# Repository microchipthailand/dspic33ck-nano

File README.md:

# dsPIC33CK Nano

An open-hardware breadboard board for the Microchip **dsPIC33CK256MC005**
(100 MIPS dsPIC DSC), with an **Arduino-compatible core** and a 30-lab course.

## 📘 Lab manual

| | |
|---|---|
| **Lab manual (English)** | [**Open the lab manual**](https://microchipthailand.github.io/dspic33ck-nano/arduino/dsPIC33CK_Nano_Labs.html): 30 step-by-step labs with wiring diagrams |
| **คู่มือการทดลอง (ภาษาไทย)** | [**เปิดคู่มือภาษาไทย**](https://microchipthailand.github.io/dspic33ck-nano/arduino/dsPIC33CK_Nano_Labs_TH.html) |
| **Pinout page** | [Board pinout and Arduino pin functions](https://microchipthailand.github.io/dspic33ck-nano/arduino/dsPIC33CK_Nano_Pinout.html) |

The labs go from *Basics* (Blink, Serial, ADC, PWM, I2C, SPI) through *Advanced*
(interrupts, timers, DMA, DAC, flash EEPROM, RTOS, watchdog) to *Application*
(data logger, GPS, WS2812B, OLED, Modbus RS485, LIN, CAN, 10BASE-T1S, line-follower
robot, PID temperature control). Every lab has objectives, background theory, a
parts list, a wiring diagram, steps, expected output, a code walk-through,
exercises and troubleshooting.

<sub>If the links above do not open, the pages are also in the repo:
[`arduino/dsPIC33CK_Nano_Labs.html`](arduino/dsPIC33CK_Nano_Labs.html) ·
[`arduino/dsPIC33CK_Nano_Labs_TH.html`](arduino/dsPIC33CK_Nano_Labs_TH.html) ·
[`arduino/dsPIC33CK_Nano_Pinout.html`](arduino/dsPIC33CK_Nano_Pinout.html)
(download, then open in a browser).</sub>

## 📌 Board pinout

Left header **J2**, right header **J3**, both numbered from the USB-C end. The rows
are 0.9" apart, so the board straddles a standard breadboard. Use the Arduino
names (`D5`, `A2`, ...) in sketches.

| Function | Arduino pin | Chip pin | Header |
|---|---|---|---|
| Power out | 3V3 (250 mA) / 5V (USB) | – | J3-1 / J2-1 |
| GND | – | – | J2-2, J3-2 |
| `LED_BUILTIN` (active low) | D34 | RC13 | J2-11 |
| `BUTTON_BUILTIN` (LOW = pressed) | D33 | RC12 | J2-10 |
| `Serial` TX / RX (115200) | D31 / D32 | RC10 / RC11 | J3-4 / J3-3, and UART header J5 |
| I2C `Wire` SDA / SCL | D14 / D13 | RB9 / RB8 | J3-7 / J3-8 |
| SPI SCK / MOSI / MISO / SS | D25 / D26 / D29 / D30 | RC4 / RC5 / RC8 / RC9 | J3-6 / J3-5 / J3-14 / J3-13 |
| `analogWrite()` PWM | D5 / D6 / D7 / D8 | RB0 / RB1 / RB2 / RB3 | J3-21 / J3-20 / J3-17 / J3-16 |
| Analog inputs A0–A4 | A0–A4 (D0–D4) | RA0–RA4 | J2-15 … J2-19 |
| Programming (PICkit / SNAP) | – | MCLR, PGD3 = RB5, PGC3 = RB6 | ICSP header J4 |

All I/O is 3.3 V. Full table with every pin and alternate function: [pinout page](https://microchipthailand.github.io/dspic33ck-nano/arduino/dsPIC33CK_Nano_Pinout.html).

| | |
|---|---|
| MCU | dsPIC33CK256MC005-I/PT, 256 KB flash, 24 KB RAM, internal FRC + PLL (no crystal) |
| Power | USB-C (power only) → MCP1703A 3.3 V LDO |
| Board | 31.4 × 74.5 mm, 2 layers, 2 × 22-pin headers 0.9" apart (fits a breadboard) |
| I/O | user LED RC13, user button RC12, reset button, ICSP header J4 (PICkit/SNAP), UART header J5 |
| Software | Arduino IDE / arduino-cli platform, serial bootloader, 30 example labs |

> **Status:** ERC/DRC clean, Gerbers generated, all labs compile and many were
> checked in the MPLAB simulator. **The board has not been built or tested on
> real hardware yet.**

## Repository layout

```
arduino/                       Arduino-compatible platform + labs + docs
  hardware/dspicnano/dspic33ck/  copy this into <sketchbook>/hardware/
  dsPIC33CK_Nano_Labs.html       step-by-step lab guide with wiring diagrams
  dsPIC33CK_Nano_Pinout.html     pinout page
  tools/                         doc / wiring-diagram generators and checks
pcb/
  kicad/                         KiCad 10 project (schematic, routed PCB, BOM, reports)
  scripts/                       Python generators (design.py = parts and nets)
  fabrication/                   Gerbers + drill (zip ready for the fab), BOM, pick-and-place, PDFs
docs/images/                   renders and pinout image used in this README
LICENSE  NOTICE.md  LICENSES/  licensing and third-party notices
```

## Quick start (Arduino)

1. Install **MPLAB XC-DSC v4.00+** (the free edition is enough) and **MPLAB X**
   (it provides IPE for PICkit uploads) from microchip.com.
2. In the Arduino IDE, open *File → Preferences → Additional boards manager URLs*
   and add:
   ```
   https://raw.githubusercontent.com/microchipthailand/dspic33ck-nano/main/package_dspicnano_index.json
   ```
3. Open *Tools → Board → Boards Manager*, search **dsPIC33CK Nano**, and click
   **Install**. The dsPIC33CK device packs are installed with it.
   (If you are developing the core, copy `arduino/hardware/` into your sketchbook
   instead. Do not use both methods at once.)
4. Pick *Tools → Board → dsPIC33CK Nano (dsPIC33CK256MC005)*, then open
   *File → Examples → dsPIC33CK_Nano → Lab01_Blink* and upload it over a PICkit on J4.

More detail: [`arduino/README.md`](arduino/README.md) and the [lab manual](https://microchipthailand.github.io/dspic33ck-nano/arduino/dsPIC33CK_Nano_Labs.html).

## Ordering the PCB

Upload `pcb/fabrication/dspic33ck_nano_gerbers.zip` to any PCB fab. Use these
settings: 2 layers, 1.6 mm, red mask, HASL. The full spec is in
[`pcb/fabrication/README.txt`](pcb/fabrication/README.txt).

> The top silkscreen has a Microchip logo. Remove it before selling boards; see
> [`NOTICE.md`](NOTICE.md).

## License

- This repository (Arduino core, variant, bootloader, labs, docs, PCB design):
  **MIT**, see [`LICENSE`](LICENSE).
- Microchip linker scripts: Apache-2.0 ([`LICENSES/Apache-2.0.txt`](LICENSES/Apache-2.0.txt)).

## Trademarks

This is an independent, Arduino-compatible project. It is not affiliated with or
endorsed by Arduino SA. "Arduino" is a trademark of Arduino SA. Microchip,
dsPIC, MPLAB, PICkit and Curiosity are trademarks of Microchip Technology Inc.

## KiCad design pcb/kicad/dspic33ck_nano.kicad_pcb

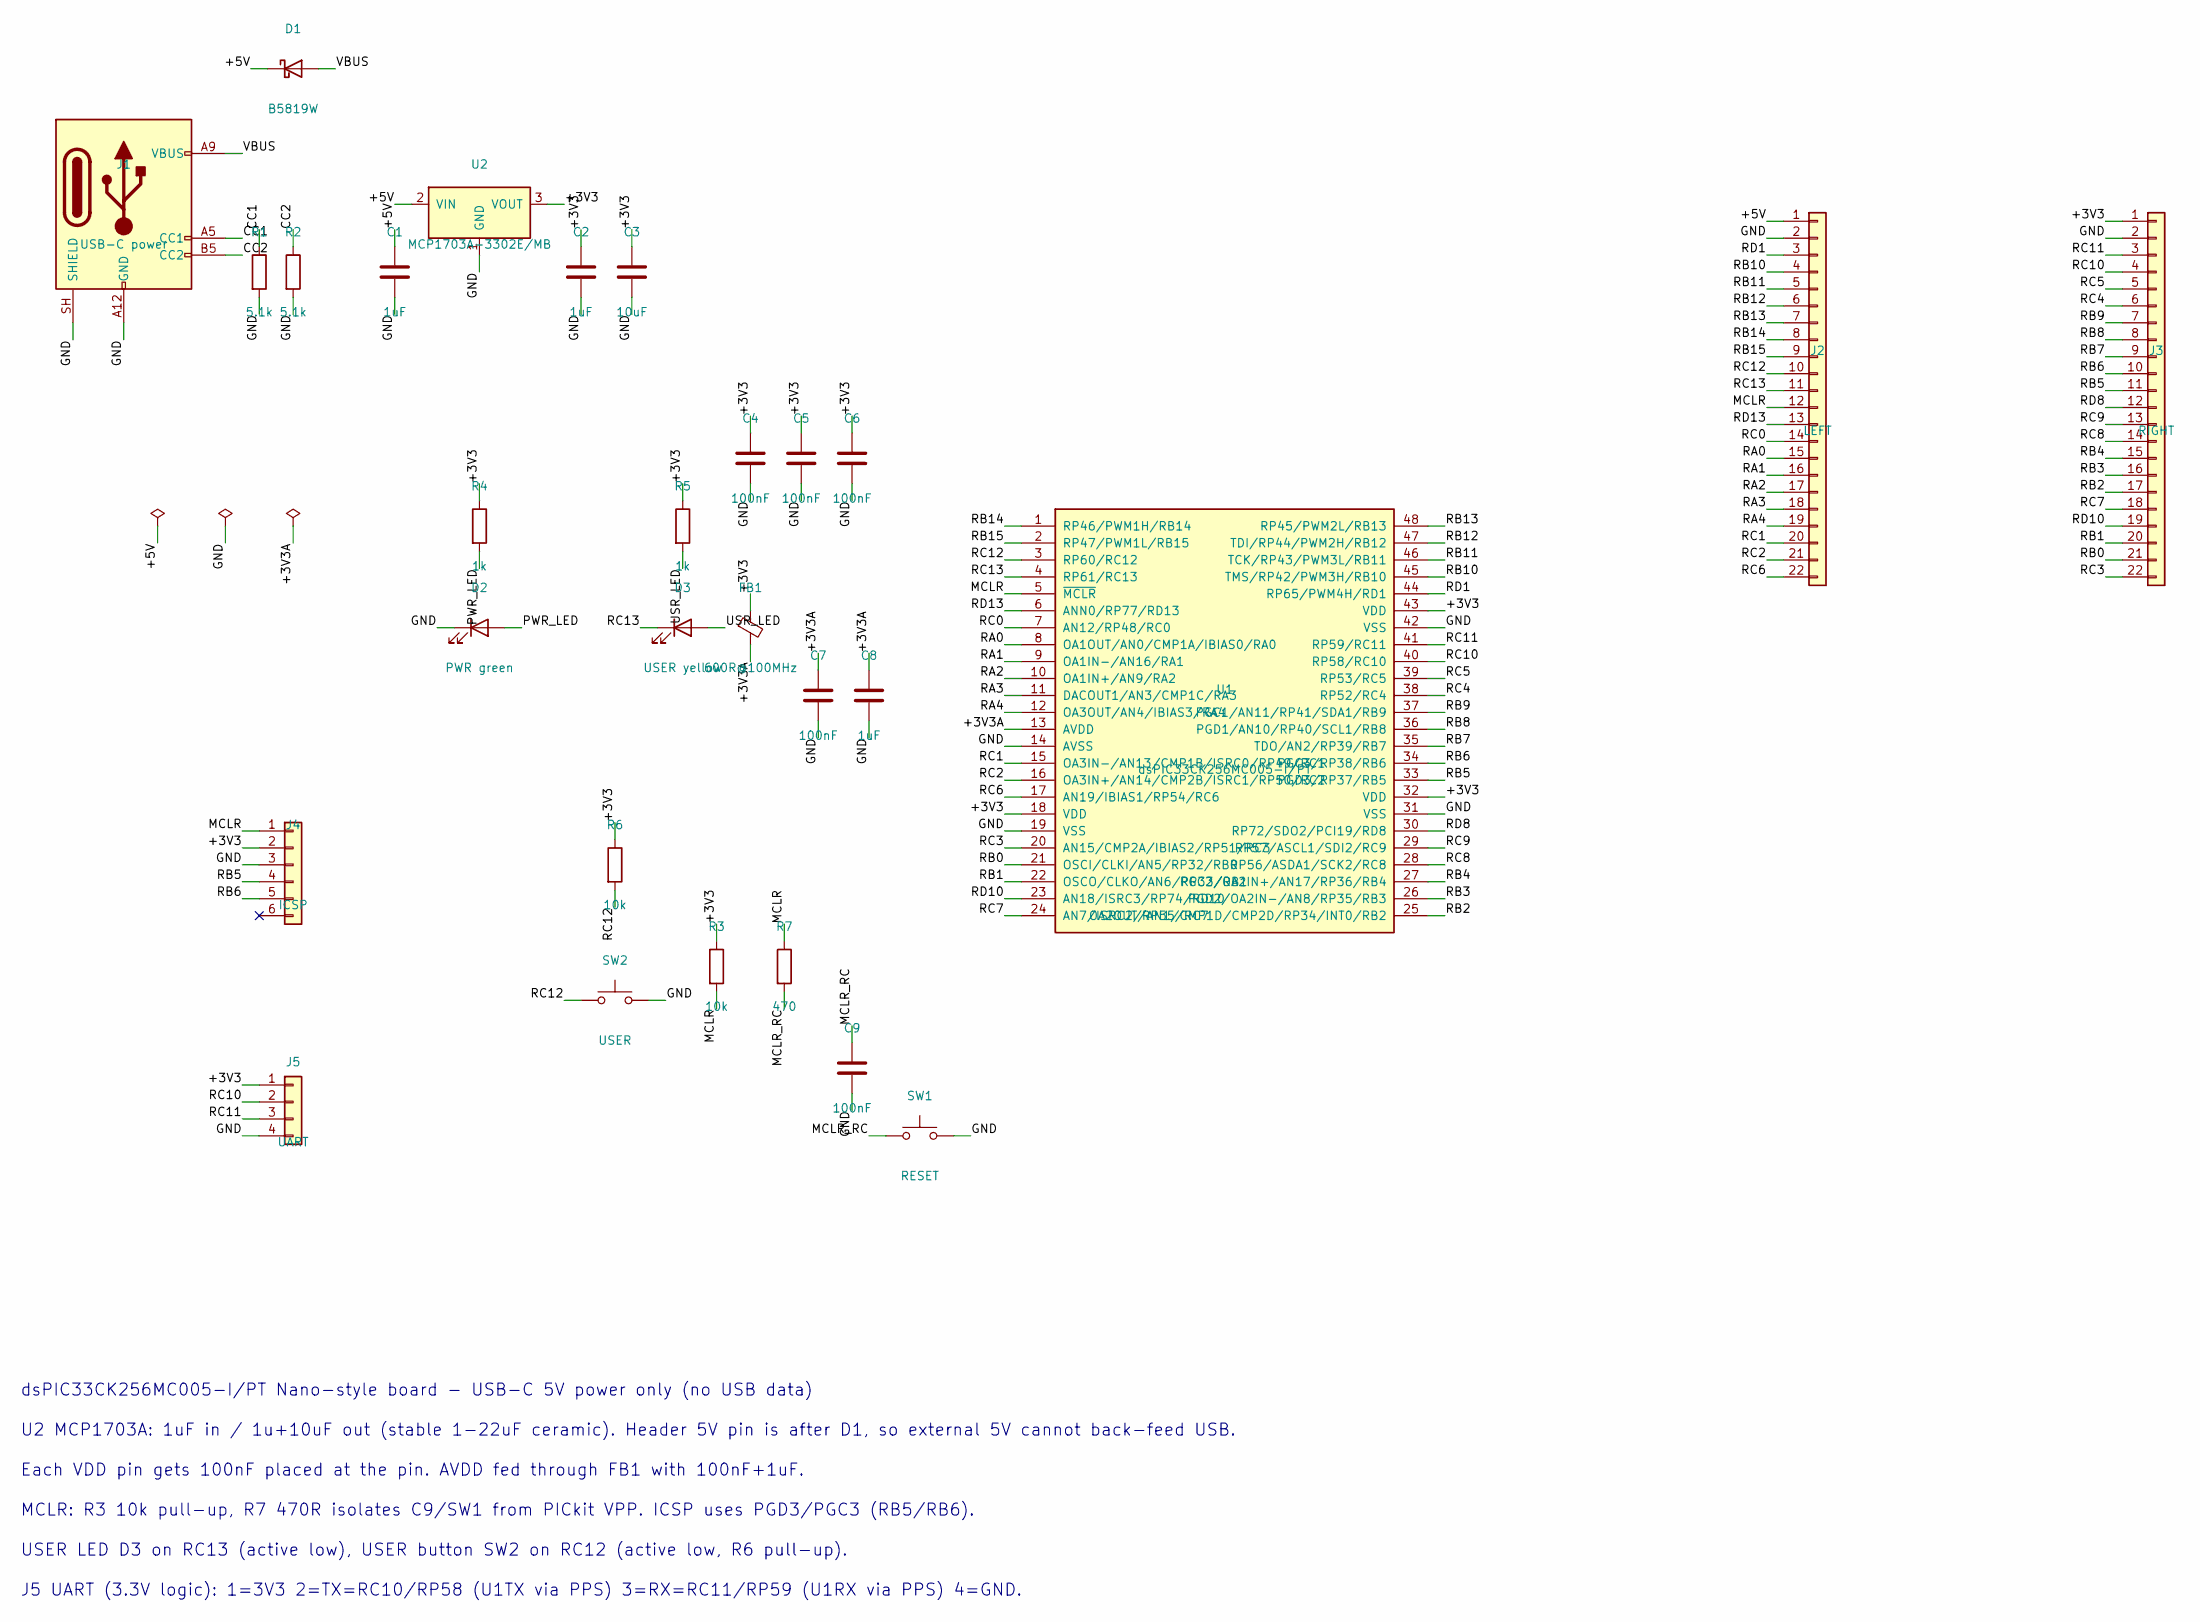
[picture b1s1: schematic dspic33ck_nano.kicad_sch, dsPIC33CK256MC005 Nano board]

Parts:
C1, C2, C8: 1uF; C_0805_2012Metric; MPN 0805 1uF 16V X7R
C3: 10uF; C_0805_2012Metric; MPN 0805 10uF 10V X5R
C4, C5, C6, C7, C9: 100nF; C_0805_2012Metric; MPN 0805 100nF 16V X7R
D1: B5819W; D_SOD-123; MPN B5819W
D2: PWR green; LED_0603_1608Metric; MPN 0603 green LED
D3: USER yellow; LED_0603_1608Metric; MPN 0603 yellow LED
FB1: 600R@100MHz; L_0603_1608Metric; MPN BLM18AG601SN1D
J1: USB-C power; USB_C_Receptacle_GCT_USB4125-xx-x-0190_6P_TopMnt_Horizontal; MPN GCT USB4125-GF-A
J2: LEFT; PinHeader_1x22_P2.54mm_Vertical; MPN 1x22 2.54mm header
J3: RIGHT; PinHeader_1x22_P2.54mm_Vertical; MPN 1x22 2.54mm header
J4: ICSP; PinHeader_1x06_P2.54mm_Vertical; MPN 1x6 2.54mm header (PICkit)
J5: UART; PinHeader_1x04_P2.54mm_Vertical; MPN 1x4 2.54mm header (UART)
R1, R2: 5.1k; R_0805_2012Metric; MPN 0805 5.1k 1%
R3, R6: 10k; R_0805_2012Metric; MPN 0805 10k 1%
R4, R5: 1k; R_0805_2012Metric; MPN 0805 1k 1%
R7: 470; R_0805_2012Metric; MPN 0805 470R 1%
SW1: RESET; SW_SPST_TL3342; MPN E-Switch TL3342 series (4.2x3.2mm SMD t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
SW2: USER; SW_SPST_TL3342; MPN E-Switch TL3342 series (4.2x3.2mm SMD t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
U1: dsPIC33CK256MC005-I/PT; TQFP-48_7x7mm_P0.5mm; MPN dsPIC33CK256MC005-I/PT
U2: MCP1703A-3302E/MB; SOT-89-3; MPN MCP1703AT-3302E/MB

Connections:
/+3V3: C2.1, C3.1, C4.1, C5.1, C6.1, FB1.1, J3.1, J4.2, J5.1, R3.1, R4.1, R5.1, R6.1, U1.18 (VDD), U1.32 (VDD), U1.43 (VDD), U2.3 (VOUT)
/+3V3A: C7.1, C8.1, FB1.2, U1.13 (AVDD)
/+5V: C1.1, D1.1 (K), J2.1, U2.2 (VIN)
/CC1: J1.A5 (CC1), R1.1
/CC2: J1.B5 (CC2), R2.1
/GND: C1.2, C2.2, C3.2, C4.2, C5.2, C6.2, C7.2, C8.2, C9.2, D2.1 (K), J1.A12 (GND), J1.B12 (GND), J1.SH (SHIELD), J2.2, J3.2, J4.3, J5.4, R1.2, R2.2, SW1.2, SW2.2, U1.14 (AVSS), U1.19 (VSS), U1.31 (VSS), U1.42 (VSS), U2.1 (GND)
/MCLR: J2.12, J4.1, R3.2, R7.1, U1.5 (~MCLR)
/MCLR_RC: C9.1, R7.2, SW1.1
/PWR_LED: D2.2 (A), R4.2
/RA0: J2.15, U1.8 (OA1OUT/AN0/CMP1A/IBIAS0/RA0)
/RA1: J2.16, U1.9 (OA1IN-/AN16/RA1)
/RA2: J2.17, U1.10 (OA1IN+/AN9/RA2)
/RA3: J2.18, U1.11 (DACOUT1/AN3/CMP1C/RA3)
/RA4: J2.19, U1.12 (OA3OUT/AN4/IBIAS3/RA4)
/RB0: J3.21, U1.21 (OSCI/CLKI/AN5/RP32/RB0)
/RB1: J3.20, U1.22 (OSCO/CLKO/AN6/RP33/RB1)
/RB2: J3.17, U1.25 (OA2OUT/AN1/CMP1D/CMP2D/RP34/INT0/RB2)
/RB3: J3.16, U1.26 (PGD2/OA2IN-/AN8/RP35/RB3)
/RB4: J3.15, U1.27 (PGC2/OA2IN+/AN17/RP36/RB4)
/RB5: J3.11, J4.4, U1.33 (PGD3/RP37/RB5)
/RB6: J3.10, J4.5, U1.34 (PGC3/RP38/RB6)
/RB7: J3.9, U1.35 (TDO/AN2/RP39/RB7)
/RB8: J3.8, U1.36 (PGD1/AN10/RP40/SCL1/RB8)
/RB9: J3.7, U1.37 (PGC1/AN11/RP41/SDA1/RB9)
/RB10: J2.4, U1.45 (TMS/RP42/PWM3H/RB10)
/RB11: J2.5, U1.46 (TCK/RP43/PWM3L/RB11)
/RB12: J2.6, U1.47 (TDI/RP44/PWM2H/RB12)
/RB13: J2.7, U1.48 (RP45/PWM2L/RB13)
/RB14: J2.8, U1.1 (RP46/PWM1H/RB14)
/RB15: J2.9, U1.2 (RP47/PWM1L/RB15)
/RC0: J2.14, U1.7 (AN12/RP48/RC0)
/RC1: J2.20, U1.15 (OA3IN-/AN13/CMP1B/ISRC0/RP49/RC1)
/RC2: J2.21, U1.16 (OA3IN+/AN14/CMP2B/ISRC1/RP50/RC2)
/RC3: J3.22, U1.20 (AN15/CMP2A/IBIAS2/RP51/RC3)
/RC4: J3.6, U1.38 (RP52/RC4)
/RC5: J3.5, U1.39 (RP53/RC5)
/RC6: J2.22, U1.17 (AN19/IBIAS1/RP54/RC6)
/RC7: J3.18, U1.24 (AN7/ISRC2/RP55/RC7)
/RC8: J3.14, U1.28 (RP56/ASDA1/SCK2/RC8)
/RC9: J3.13, U1.29 (RP57/ASCL1/SDI2/RC9)
/RC10: J3.4, J5.2, U1.40 (RP58/RC10)
/RC11: J3.3, J5.3, U1.41 (RP59/RC11)
/RC12: J2.10, R6.2, SW2.1, U1.3 (RP60/RC12)
/RC13: D3.1 (K), J2.11, U1.4 (RP61/RC13)
/RD1: J2.3, U1.44 (RP65/PWM4H/RD1)
/RD8: J3.12, U1.30 (RP72/SDO2/PCI19/RD8)
/RD10: J3.19, U1.23 (AN18/ISRC3/RP74/RD10)
/RD13: J2.13, U1.6 (ANN0/RP77/RD13)
/USR_LED: D3.2 (A), R5.2
/VBUS: D1.2 (A), J1.A9 (VBUS), J1.B9 (VBUS)

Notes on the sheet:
dsPIC33CK256MC005-I/PT Nano-style board - USB-C 5V power only (no USB data)
U2 MCP1703A: 1uF in / 1u+10uF out (stable 1-22uF ceramic). Header 5V pin is after D1, so external 5V cannot back-feed USB.
Each VDD pin gets 100nF placed at the pin. AVDD fed through FB1 with 100nF+1uF.
MCLR: R3 10k pull-up, R7 470R isolates C9/SW1 from PICkit VPP. ICSP uses PGD3/PGC3 (RB5/RB6).
USER LED D3 on RC13 (active low), USER button SW2 on RC12 (active low, R6 pull-up).
J5 UART (3.3V logic): 1=3V3 2=TX=RC10/RP58 (U1TX via PPS) 3=RX=RC11/RP59 (U1RX via PPS) 4=GND.

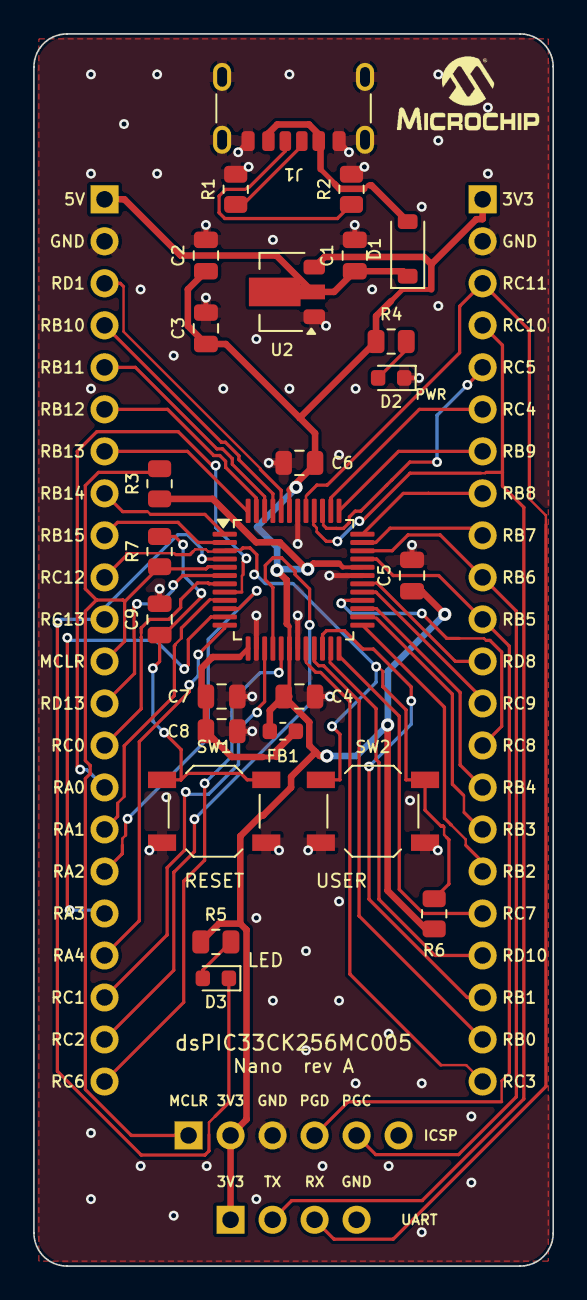
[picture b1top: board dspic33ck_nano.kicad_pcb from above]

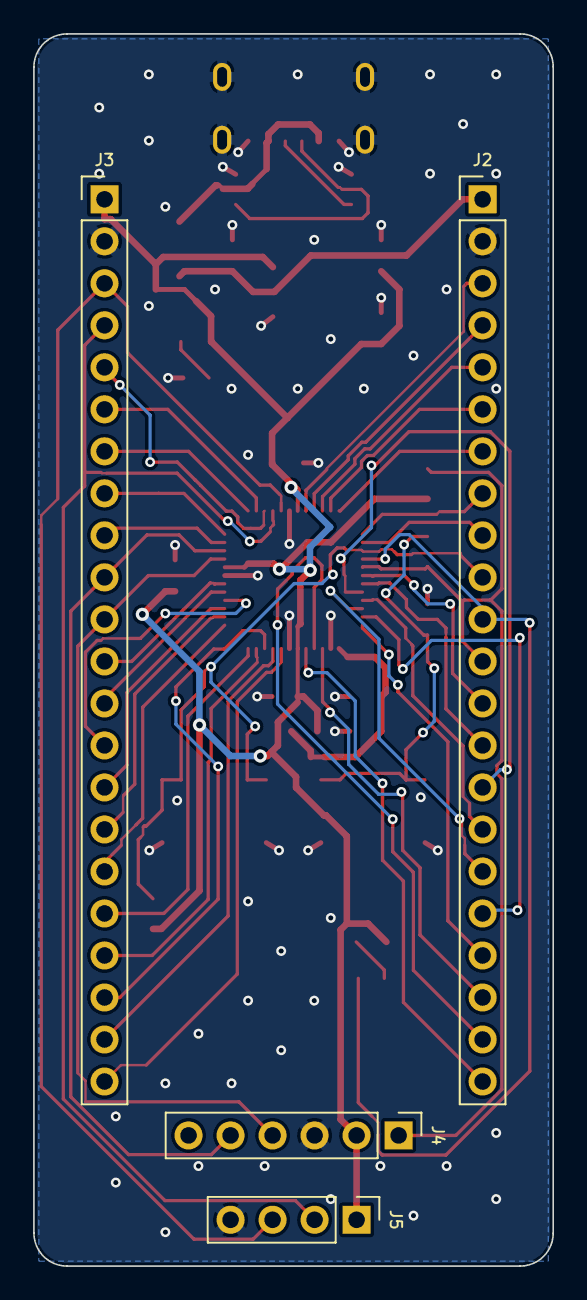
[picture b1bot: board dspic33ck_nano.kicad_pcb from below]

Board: 2 copper layers, 31.4 x 74.5 mm, 30 parts (4 on the bottom side), 50 nets.

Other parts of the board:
LOGO1: Microchip_Logo

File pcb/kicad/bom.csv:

Refs,Value,Footprint,MPN,Qty,Cost/pcUSD,,Total/USD
"C1,C2,C8",1uF,Capacitor_SMD:C_0805_2012Metric,0805 1uF 16V X7R,3,0.01,0.33,0.03
C3,10uF,Capacitor_SMD:C_0805_2012Metric,0805 10uF 10V X5R,1,0.01,0.33,0.01
"C4-C7,C9",100nF,Capacitor_SMD:C_0805_2012Metric,0805 100nF 16V X7R,5,0.05,1.65,0.25
D1,B5819W,Diode_SMD:D_SOD-123,B5819W,1,0.05,1.65,0.05
D2,PWR green,LED_SMD:LED_0603_1608Metric,0603 green LED,1,0.02,0.66,0.02
D3,USER yellow,LED_SMD:LED_0603_1608Metric,0603 yellow LED,1,0.02,0.66,0.02
FB1,600R@100MHz,Inductor_SMD:L_0603_1608Metric,BLM18AG601SN1D,1,0.02,0.66,0.02
J1,USB-C power,Connector_USB:USB_C_Receptacle_GCT_USB4125-xx-x-0190_6P_TopMnt_Horizontal,GCT USB4125-GF-A,1,0.05,1.65,0.05
J2,LEFT,Connector_PinHeader_2.54mm:PinHeader_1x22_P2.54mm_Vertical,1x22 2.54mm header,1,,0,
J3,RIGHT,Connector_PinHeader_2.54mm:PinHeader_1x22_P2.54mm_Vertical,1x22 2.54mm header,1,,0,
J4,ICSP,Connector_PinHeader_2.54mm:PinHeader_1x06_P2.54mm_Vertical,1x6 2.54mm header (PICkit),1,,0,
J5,UART,Connector_PinHeader_2.54mm:PinHeader_1x04_P2.54mm_Vertical,1x4 2.54mm header (UART),1,,0,
"R1,R2",5.1k,Resistor_SMD:R_0805_2012Metric,0805 5.1k 1%,2,0.01,0.33,0.02
"R3,R6",10k,Resistor_SMD:R_0805_2012Metric,0805 10k 1%,2,0.01,0.33,0.02
"R4,R5",1k,Resistor_SMD:R_0805_2012Metric,0805 1k 1%,2,0.01,0.33,0.02
R7,470,Resistor_SMD:R_0805_2012Metric,0805 470R 1%,1,0.01,0.33,0.01
SW1,RESET,Button_Switch_SMD:SW_SPST_TL3342,E-Switch TL3342 series (4.2x3.2mm SMD tact),1,0.05,1.65,0.05
SW2,USER,Button_Switch_SMD:SW_SPST_TL3342,E-Switch TL3342 series (4.2x3.2mm SMD tact),1,0.05,1.65,0.05
U1,dsPIC33CK256MC005-I/PT,Package_QFP:TQFP-48_7x7mm_P0.5mm,dsPIC33CK256MC005-I/PT,1,0.75,24.75,0.75
U2,MCP1703A-3302E/MB,Package_TO_SOT_SMD:SOT-89-3,MCP1703AT-3302E/MB,1,0.25,8.25,0.25
,,PCB,,1,0.3,9.9,0.3
,,PCB assembly ,,1,0.3,9.9,0.3
,,,,Grand Total  - USD,,,2.22

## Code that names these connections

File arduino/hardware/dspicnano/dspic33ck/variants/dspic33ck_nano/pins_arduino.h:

/*
 * pins_arduino.h - Pin mapping for dsPIC33CK256MC005
 *
 * dsPIC33CK256MC005 is a 48-pin TQFP Value Line Motor Control device with:
 *   - PORTA: RA0-RA4        (5 pins, all analog-capable, NOT remappable)
 *   - PORTB: RB0-RB15       (16 pins, RP32-RP47)
 *   - PORTC: RC0-RC13       (14 pins, RP48-RP61)
 *   - PORTD: RD1, RD8, RD10, RD13 only (RP65, RP72, RP74, RP77)
 *   - 256KB Flash (ECC), 16KB RAM
 *   - SCCP1-4, PWM generators PG1-PG4, U1-U3, SPI1-2, I2C1, DAC1
 *   - DFP: dsPIC33CK-MC_DFP >= 1.10.386 (earlier packs have no MC005)
 *   - Board: dsPIC33CK Nano (custom breadboard board)
 *
 * Board: dsPIC33CK Nano (custom, 31.4 x 74.5 mm) - NOT the EV08P02A.
 * Wiring taken from the board's KiCad netlist (pcb_scripts/design.py):
 *   USER LED  = RC13 (D34), ACTIVE LOW: 3V3 -> R5 1k -> LED -> RC13
 *   USER SW2  = RC12 (D33), EXTERNAL 10k pull-up (R6), reads LOW when pressed
 *   RESET SW1 = MCLR (R3 10k pull-up, R7 470R + C9 100nF)
 *   UART J5   = 1:3V3  2:TX = U1TX RC10 (RP58)  3:RX = U1RX RC11 (RP59)  4:GND
 *               -> connect a 3.3 V USB-serial adapter (adapter RX to J5-2)
 *   ICSP J4   = 1:MCLR 2:3V3 3:GND 4:PGD3=RB5 5:PGC3=RB6 6:nc
 *               RB5/RB6 are free I/O when no debugger is attached, but the
 *               debugger drives them while programming.
 *   PWR LED   = hard-wired to 3V3 (not controllable)
 *   No crystal: RB0/RB1 (OSCI/OSCO) are ordinary I/O.
 *   ALTI2C1   = OFF, so I2C1 uses SDA1 = RB9, SCL1 = RB8
 *
 * Arduino Pin Mapping (contiguous over bonded pins only):
 *   D0-D4   = RA0-RA4
 *   D5-D20  = RB0-RB15
 *   D21-D34 = RC0-RC13
 *   D35     = RD1
 *   D36     = RD8
 *   D37     = RD10  (LED0)
 *   D38     = RD13  (SW0)
 *
 * Analog Inputs (20 channels, mapping taken from the device's edc pin database
 * DSPIC33CK256MC005.PIC — note it differs from MP508 and MC002):
 *   A0 =RA0(AN0)   A1 =RA1(AN16)  A2 =RA2(AN9)   A3 =RA3(AN3)   A4 =RA4(AN4)
 *   A5 =RB0(AN5)   A6 =RB1(AN6)   A7 =RB2(AN1)   A8 =RB3(AN8)   A9 =RB4(AN17)
 *   A10=RB7(AN2)   A11=RB8(AN10)  A12=RB9(AN11)
 *   A13=RC0(AN12)  A14=RC1(AN13)  A15=RC2(AN14)  A16=RC3(AN15)
 *   A17=RC6(AN19)  A18=RC7(AN7)   A19=RD10(AN18)
 *   RD13 is ANN0 (ADC negative input only) and is NOT an analog input here.
 *
 * PWM Pins: D5(RB0), D6(RB1), D7(RB2), D8(RB3) via SCCP1-4.
 *           This part has only CCP1-4 — there is no PWM5 (unlike MP508).
 * UART TX:  D31 (RC10/RP58 via PPS - header J5 pin 2)
 * UART RX:  D32 (RC11/RP59 via PPS - header J5 pin 3)
 * SPI:      SCK=D25(RC4) MOSI=D26(RC5) MISO=D29(RC8) SS=D30(RC9)
 *           (EV08P02A used RC12/RC13 for MISO/SS - on this board those are
 *           the USER button and LED, so MISO/SS moved to RC8/RC9.)
 * I2C:      SDA=D14(RB9), SCL=D13(RB8) — dedicated I2C1 pins, no PPS
 */

#ifndef PINS_ARDUINO_H
#define PINS_ARDUINO_H

#include <stdint.h>

#define NUM_DIGITAL_PINS    39
#define NUM_ANALOG_INPUTS   20
#define NUM_PWM_PINS        4

/* Board identification */
#define ARDUINO_DSPIC33CK_NANO_BOARD 1

/* LED_BUILTIN - RC13 (USER LED D3). ACTIVE LOW: the LED's cathode is on the
 * pin, so digitalWrite(LED_BUILTIN, LOW) turns it ON. Stock Blink still blinks. */
#define LED_BUILTIN             34
#define LED_USER                34
#define LED0                    34
#define LED_BUILTIN_ACTIVE_LOW  1
#define LED_ON                  LOW
#define LED_OFF                 HIGH

/* USER button SW2 - RC12. External 10k pull-up (R6) to 3V3, reads LOW when
 * pressed. INPUT_PULLUP is harmless but not required. */
#define BUTTON_BUILTIN          33
#define BUTTON_USER             33
#define SW0                     33
#define BUTTON_BUILTIN_ACTIVE_LOW 1

/* Header J5 (UART) and J4 (ICSP) pins, by Arduino number */
#define PIN_J5_TX               31  /* RC10 */
#define PIN_J5_RX               32  /* RC11 */
#define PIN_PGD3                10  /* RB5 - J4 pin 4 */
#define PIN_PGC3                11  /* RB6 - J4 pin 5 */

/* Analog pin aliases (PORTA) */
#define A0  0   /* RA0 = AN0  */
#define A1  1   /* RA1 = AN16 */
#define A2  2   /* RA2 = AN9  */
#define A3  3   /* RA3 = AN3  */
#define A4  4   /* RA4 = AN4  */

/* Analog pin aliases (PORTB) */
#define A5  5   /* RB0 = AN5  */
#define A6  6   /* RB1 = AN6  */
#define A7  7   /* RB2 = AN1  */
#define A8  8   /* RB3 = AN8  */
#define A9  9   /* RB4 = AN17 */
#define A10 12  /* RB7 = AN2  */
#define A11 13  /* RB8 = AN10 — also I2C1 SCL1 */
#define A12 14  /* RB9 = AN11 — also I2C1 SDA1 */

/* Analog pin aliases (PORTC) */
#define A13 21  /* RC0 = AN12 */
#define A14 22  /* RC1 = AN13 */
#define A15 23  /* RC2 = AN14 */
#define A16 24  /* RC3 = AN15 */
#define A17 27  /* RC6 = AN19 */
#define A18 28  /* RC7 = AN7  */

/* Analog pin alias (PORTD) */
#define A19 37  /* RD10 = AN18 */

/* SPI pin definitions (SPI1 via PPS). RC4/RC5/RC8/RC9 = J3 pins 6/5/14/13. */
#define PIN_SPI_SS          30  /* RC9  */
#define PIN_SPI_MOSI        26  /* RC5  */
#define PIN_SPI_MISO        29  /* RC8  */
#define PIN_SPI_SCK         25  /* RC4  */

static const uint8_t SS   = PIN_SPI_SS;
static const uint8_t MOSI = PIN_SPI_MOSI;
static const uint8_t MISO = PIN_SPI_MISO;
static const uint8_t SCK  = PIN_SPI_SCK;

/* SPI PPS mapping macros */
#define SPI_SCK_RP_REG      _RP52R      /* PPS output register for RC4  (SCK1) */
#define SPI_MOSI_RP_REG     _RP53R      /* PPS output register for RC5  (SDO1) */
#define SPI_MISO_RP_NUM     56          /* RP number for RC8 (SDI1 input)  */
#define SPI_SS_RP_REG       _RP57R      /* PPS output register for RC9  (SS1) */
#define SPI_SCK_TRIS        TRISCbits.TRISC4
#define SPI_MOSI_TRIS       TRISCbits.TRISC5
#define SPI_MISO_TRIS       TRISCbits.TRISC8
#define SPI_SS_TRIS         TRISCbits.TRISC9
/* RC8 has no analog function, so no SPI_MISO_ANSEL */

/* I2C pin definitions (dedicated I2C1 pins, no PPS needed).
 * ALTI2C1 must stay OFF (the default in cores/arduino/system_config.c). */
#define PIN_WIRE_SDA        14  /* RB9 = SDA1 */
#define PIN_WIRE_SCL        13  /* RB8 = SCL1 */
#define WIRE_SDA_TRIS       TRISBbits.TRISB9
#define WIRE_SCL_TRIS       TRISBbits.TRISB8

static const uint8_t SDA = PIN_WIRE_SDA;
static const uint8_t SCL = PIN_WIRE_SCL;

/* Serial pin definitions - UART header J5 (use a 3.3 V USB-serial adapter) */
#define PIN_SERIAL_TX       31  /* RC10 */
#define PIN_SERIAL_RX       32  /* RC11 */
#define SERIAL_TX_RP_REG    _RP58R  /* PPS output register for RC10 */
#define SERIAL_RX_RP_NUM    59      /* RP number for RC11 input */
#define SERIAL_TX_TRIS      TRISCbits.TRISC10
#define SERIAL_RX_TRIS      TRISCbits.TRISC11
/* #define SERIAL_RX_ANSEL  — RC11 has no analog function, always digital */

/* ============================================================
 * Internal pin table structure
 * Each Arduino pin maps to a PORT register and bit position
 * ============================================================ */

typedef struct {
    volatile uint16_t *port_reg;   /* PORTx register */
    volatile uint16_t *tris_reg;   /* TRISx register */
    volatile uint16_t *lat_reg;    /* LATx register */
    volatile uint16_t *ansel_reg;  /* ANSELx register (NULL if no analog) */
    uint8_t bit;                   /* bit position 0-15 */
    int8_t  adc_channel;           /* ADC channel or -1 if none */
} pin_map_t;

/* Port register addresses (defined in variant.c) */
#ifdef __cplusplus
extern "C" {
#endif
extern const pin_map_t g_pin_map[];
#ifdef __cplusplus
}
#endif

/* PWM capable pins */
#define digitalPinHasPWM(p) ((p) >= 5 && (p) <= 8)

/* Every pin can carry an interrupt (Change Notification covers all ports), so
 * this is the identity -- it exists only so sketches written for AVR, where the
 * mapping is real, compile unchanged. attachInterrupt() takes the pin number. */
#define digitalPinToInterrupt(p) (((p) < NUM_DIGITAL_PINS) ? (int)(p) : -1)

/* Analog channel for a pin (-1 if not analog) */
#define analogPinToChannel(p) (g_pin_map[p].adc_channel)

/* PPS output function codes (from device header _RPOUT_ defines) */
#define PPS_OUT_U1TX    1
#define PPS_OUT_U1RTS   2
#define PPS_OUT_U2TX    3
#define PPS_OUT_SDO1    5
#define PPS_OUT_SCK1OUT 6
#define PPS_OUT_SS1OUT  7
#define PPS_OUT_OCM1    15  /* SCCP1 Output Compare */
#define PPS_OUT_OCM2    16  /* SCCP2 Output Compare */
#define PPS_OUT_OCM3    17  /* SCCP3 Output Compare */
#define PPS_OUT_OCM4    18  /* SCCP4 Output Compare */
/* No OCM5/OCM6 — dsPIC33CK256MC005 has only SCCP1-4 */

/* PWM pin definitions: Arduino pin, RP number, SCCP module */
#define PWM1_PIN        5   /* D5 = RB0 */
#define PWM1_RP         32  /* RP32 */
#define PWM2_PIN        6   /* D6 = RB1 */
#define PWM2_RP         33  /* RP33 */
#define PWM3_PIN        7   /* D7 = RB2 */
#define PWM3_RP         34  /* RP34 */
#define PWM4_PIN        8   /* D8 = RB3 */
#define PWM4_RP         35  /* RP35 */

#endif /* PINS_ARDUINO_H */

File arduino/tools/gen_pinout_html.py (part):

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<div class="legend">
  <div><span class="c d">D0</span>Arduino digital pin</div>
  <div><span class="c a">A0</span>analogRead() name</div>
  <div><span class="c port">RA0</span>chip port pin (silkscreen)</div>
  <div><span class="c an">AN0</span>ADC channel</div>
  <div><span class="c pwm">~PWM</span>analogWrite()</div>
  <div><span class="c uart">Serial</span>UART1</div>
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<tr><td>RESET button (SW1)</td><td>MCLR (10 k pull-up, 470 &Omega; + 100 nF)</td></tr>
</table>
<table class="specs">
<tr><td>J4 ICSP (6-pin)</td><td>1 MCLR &middot; 2 3V3 &middot; 3 GND &middot; 4 PGD3 (RB5) &middot; 5 PGC3 (RB6) &middot; 6 n/c &mdash; PICkit 4/5, SNAP</td></tr>
<tr><td>J5 UART (4-pin)</td><td>1 3V3 &middot; 2 TX (RC10) &middot; 3 RX (RC11) &middot; 4 GND &mdash; 3.3 V USB-serial adapter</td></tr>
<tr><td>PWM</td><td>D5 D6 D7 D8 (SCCP1-4, ~490 Hz)</td></tr>
<tr><td>Interrupts</td><td><code>attachInterrupt()</code> on every pin (change notification)</td></tr>
<tr><td>Board size</td><td>31.4 &times; 74.5 mm, 2 &times; 22 pins, red PCB</td></tr>
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<ul>
<li><b>tone()</b> borrows timer SCCP4, which is the PWM of D{TONE_PWM}. Don't use <code>analogWrite({TONE_PWM}, &hellip;)</code> while a tone plays.</li>
<li><b>RB5/RB6</b> (D10/D11) are the ICSP lines. They are free I/O when no debugger is connected, but anything wired there can disturb programming.</li>
<li><b>RB10&ndash;RB15, RD1</b> are the motor-control PWM pins of the chip (PWM1H..PWM4H); in Arduino they are ordinary digital I/O.</li>
<li><b>PORTA</b> (RA0&ndash;RA4) has no PPS, so no remappable peripheral can use it; it is the best place for analog inputs.</li>
</ul>
</section>
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<li>Install <b>XC-DSC v4.00+</b> (compiler) and <b>MPLAB X</b> (for uploading with a PICkit/SNAP).</li>
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<li><i>Tools &gt; Board</i> &rarr; <b>dsPIC33CK Nano (dsPIC33CK256MC005)</b>. <i>Tools &gt; Debugger</i> &rarr; the programmer you have on J4.</li>
<li>Power the board from USB-C, plug the PICkit into J4 (pin 1 = MCLR, square pad), and upload <i>File &gt; Examples &gt; dsPIC33CK_Nano &gt; Lab01_Blink</i>.</li>
</ol>
<h3>Optional: upload over the J5 serial port (no PICkit)</h3>
<ol>
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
